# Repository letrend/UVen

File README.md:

# UVen
UV irradiation system for enhanced photo-activation in living cells

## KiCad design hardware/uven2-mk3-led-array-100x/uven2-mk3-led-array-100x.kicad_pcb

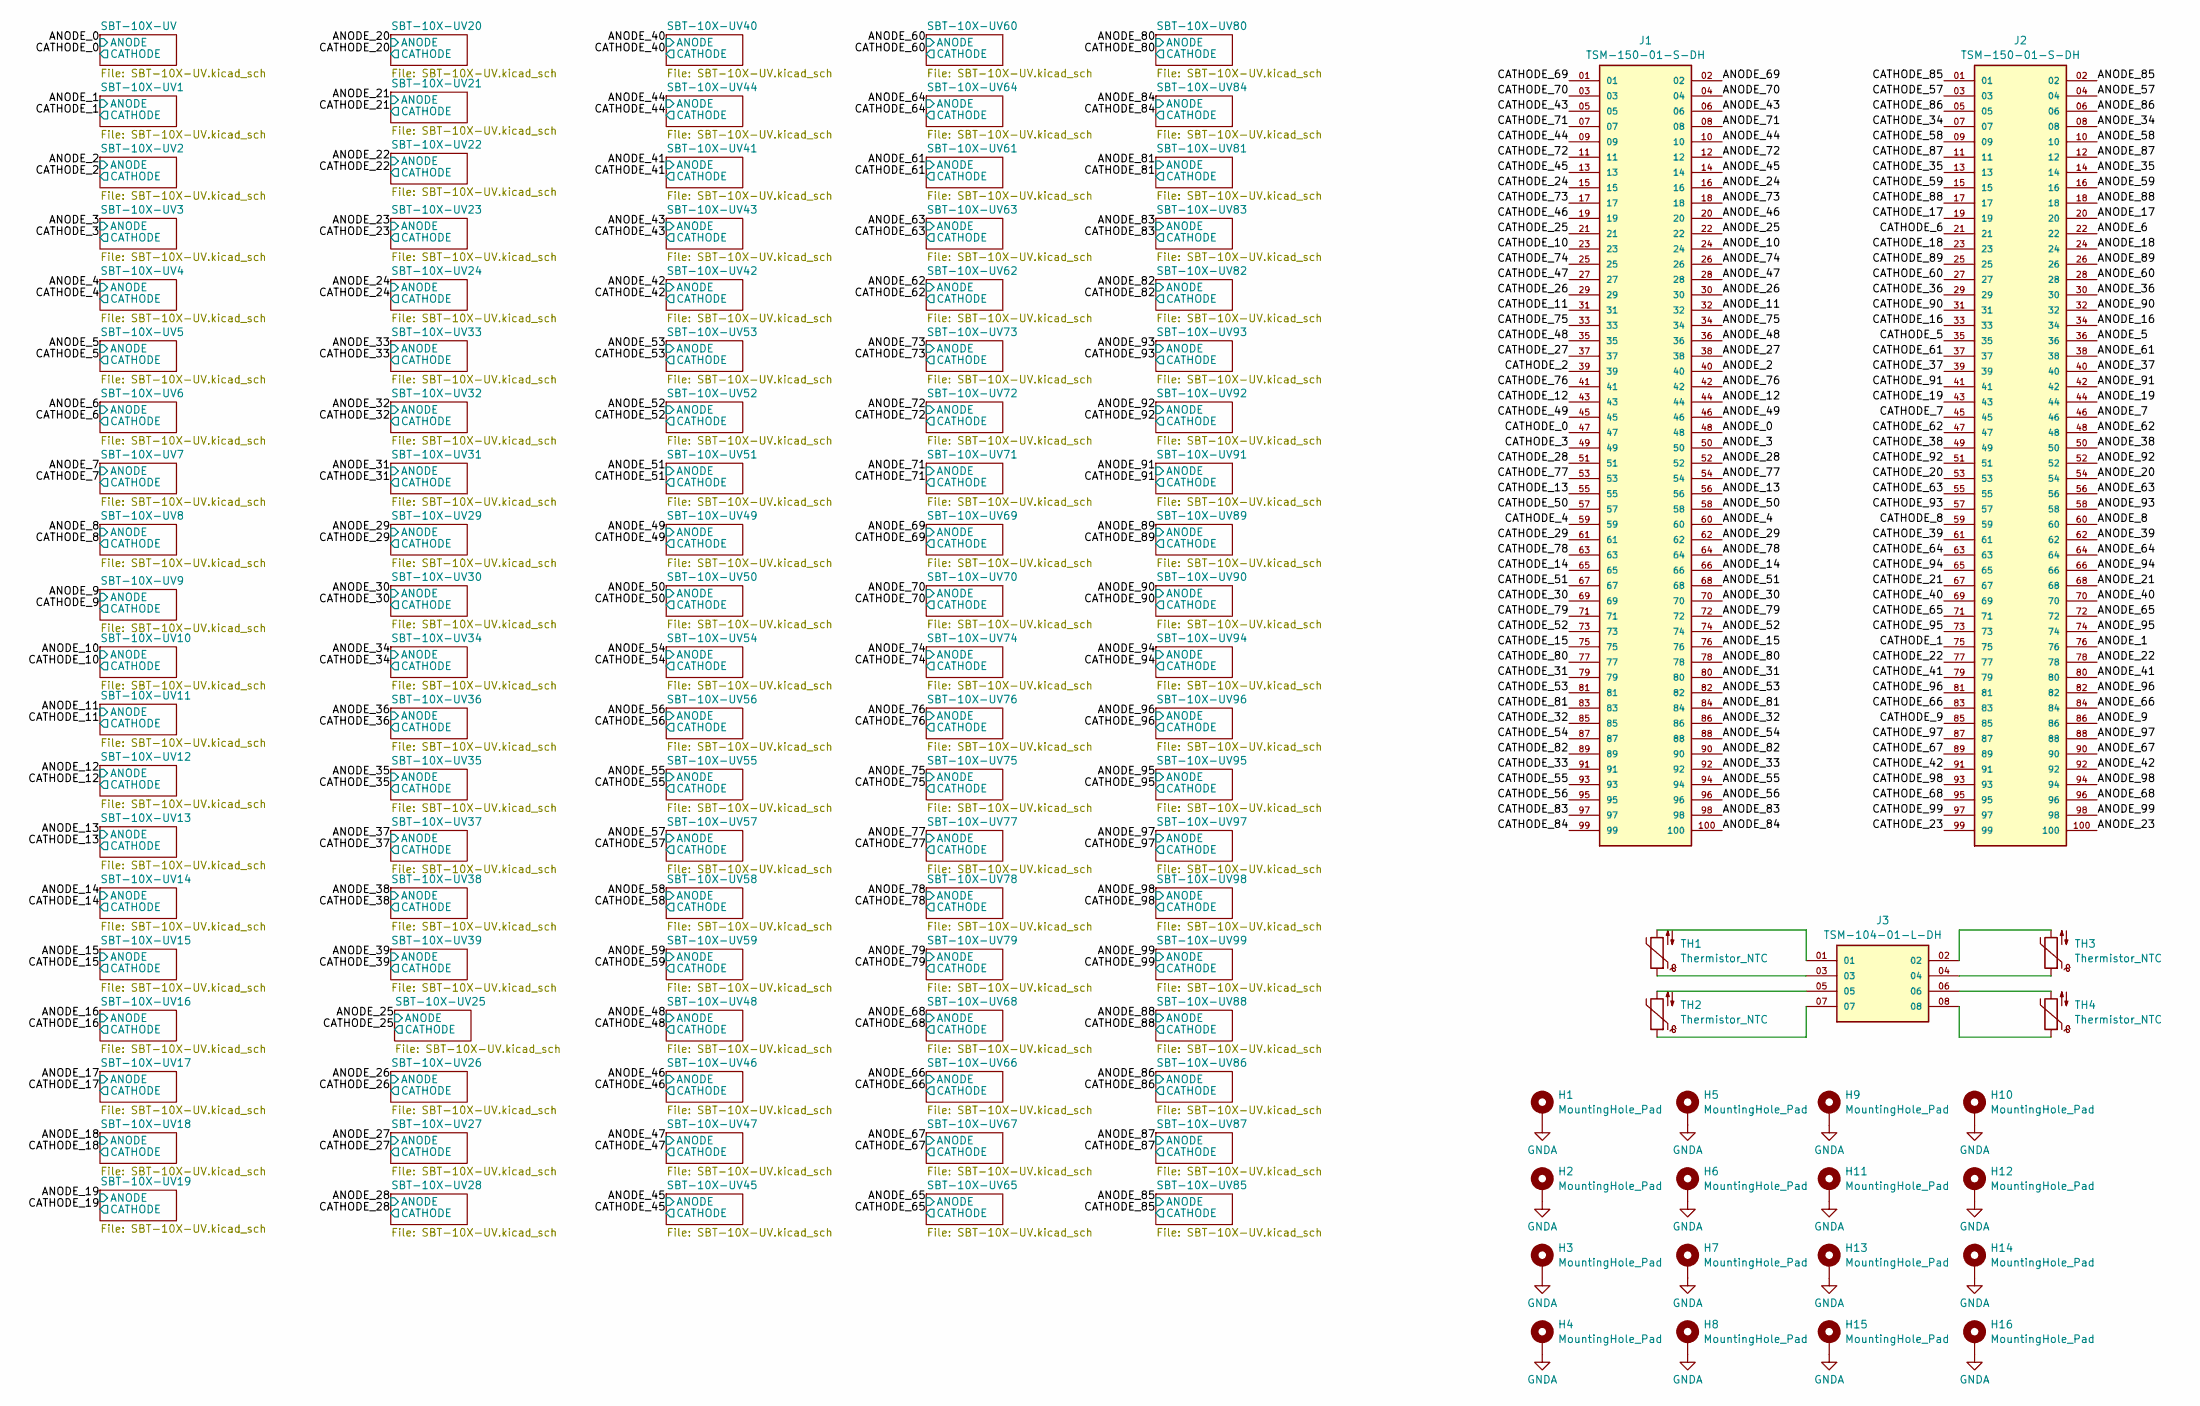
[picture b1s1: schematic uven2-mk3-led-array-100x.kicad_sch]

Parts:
H1, H2, H3, H4, H5, H6, H7, H8, H9, H10, H11, H12, H13, H14, H15, H16: MountingHole_Pad; MountingHole_3.2mm_M3_DIN965_Pad
J1, J2: TSM-150-01-S-DH; SAMTEC_TSM-150-01-S-DH; PARTREV R
J3: TSM-104-01-L-DH; SAMTEC_TSM-104-01-L-DH; PARTREV R
TH1, TH2, TH3, TH4: Thermistor_NTC; R_0805_2012Metric

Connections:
/ANODE_0: J1.48; also elsewhere on the board
/ANODE_1: J2.76; also elsewhere on the board
/ANODE_2: J1.40; also elsewhere on the board
/ANODE_3: J1.50; also elsewhere on the board
/ANODE_4: J1.60; also elsewhere on the board
/ANODE_5: J2.36; also elsewhere on the board
/ANODE_6: J2.22; also elsewhere on the board
/ANODE_7: J2.46; also elsewhere on the board
/ANODE_8: J2.60; also elsewhere on the board
/ANODE_9: J2.86; also elsewhere on the board
/ANODE_10: J1.24; also elsewhere on the board
/ANODE_11: J1.32; also elsewhere on the board
/ANODE_12: J1.44; also elsewhere on the board
/ANODE_13: J1.56; also elsewhere on the board
/ANODE_14: J1.66; also elsewhere on the board
/ANODE_15: J1.76; also elsewhere on the board
/ANODE_16: J2.34; also elsewhere on the board
/ANODE_17: J2.20; also elsewhere on the board
/ANODE_18: J2.24; also elsewhere on the board
/ANODE_19: J2.44; also elsewhere on the board
/ANODE_20: J2.54; also elsewhere on the board
/ANODE_21: J2.68; also elsewhere on the board
/ANODE_22: J2.78; also elsewhere on the board
/ANODE_23: J2.100; also elsewhere on the board
/ANODE_24: J1.16; also elsewhere on the board
/ANODE_25: J1.22; also elsewhere on the board
/ANODE_26: J1.30; also elsewhere on the board
/ANODE_27: J1.38; also elsewhere on the board
/ANODE_28: J1.52; also elsewhere on the board
/ANODE_29: J1.62; also elsewhere on the board
/ANODE_30: J1.70; also elsewhere on the board
/ANODE_31: J1.80; also elsewhere on the board
/ANODE_32: J1.86; also elsewhere on the board
/ANODE_33: J1.92; also elsewhere on the board
/ANODE_34: J2.08; also elsewhere on the board
/ANODE_35: J2.14; also elsewhere on the board
/ANODE_36: J2.30; also elsewhere on the board
/ANODE_37: J2.40; also elsewhere on the board
/ANODE_38: J2.50; also elsewhere on the board
/ANODE_39: J2.62; also elsewhere on the board
/ANODE_40: J2.70; also elsewhere on the board
/ANODE_41: J2.80; also elsewhere on the board
/ANODE_42: J2.92; also elsewhere on the board
/ANODE_43: J1.06; also elsewhere on the board
/ANODE_44: J1.10; also elsewhere on the board
/ANODE_45: J1.14; also elsewhere on the board
/ANODE_46: J1.20; also elsewhere on the board
/ANODE_47: J1.28; also elsewhere on the board
/ANODE_48: J1.36; also elsewhere on the board
/ANODE_49: J1.46; also elsewhere on the board
/ANODE_50: J1.58; also elsewhere on the board
/ANODE_51: J1.68; also elsewhere on the board
/ANODE_52: J1.74; also elsewhere on the board
/ANODE_53: J1.82; also elsewhere on the board
/ANODE_54: J1.88; also elsewhere on the board
/ANODE_55: J1.94; also elsewhere on the board
/ANODE_56: J1.96; also elsewhere on the board
/ANODE_57: J2.04; also elsewhere on the board
/ANODE_58: J2.10; also elsewhere on the board
/ANODE_59: J2.16; also elsewhere on the board
/ANODE_60: J2.28; also elsewhere on the board
/ANODE_61: J2.38; also elsewhere on the board
/ANODE_62: J2.48; also elsewhere on the board
/ANODE_63: J2.56; also elsewhere on the board
/ANODE_64: J2.64; also elsewhere on the board
/ANODE_65: J2.72; also elsewhere on the board
/ANODE_66: J2.84; also elsewhere on the board
/ANODE_67: J2.90; also elsewhere on the board
/ANODE_68: J2.96; also elsewhere on the board
/ANODE_69: J1.02; also elsewhere on the board
/ANODE_70: J1.04; also elsewhere on the board
/ANODE_71: J1.08; also elsewhere on the board
/ANODE_72: J1.12; also elsewhere on the board
/ANODE_73: J1.18; also elsewhere on the board
/ANODE_74: J1.26; also elsewhere on the board
/ANODE_75: J1.34; also elsewhere on the board
/ANODE_76: J1.42; also elsewhere on the board
/ANODE_77: J1.54; also elsewhere on the board
/ANODE_78: J1.64; also elsewhere on the board
/ANODE_79: J1.72; also elsewhere on the board
/ANODE_80: J1.78; also elsewhere on the board
/ANODE_81: J1.84; also elsewhere on the board
/ANODE_82: J1.90; also elsewhere on the board
/ANODE_83: J1.98; also elsewhere on the board
/ANODE_84: J1.100; also elsewhere on the board
/ANODE_85: J2.02; also elsewhere on the board
/ANODE_86: J2.06; also elsewhere on the board
/ANODE_87: J2.12; also elsewhere on the board
/ANODE_88: J2.18; also elsewhere on the board
/ANODE_89: J2.26; also elsewhere on the board
/ANODE_90: J2.32; also elsewhere on the board
/ANODE_91: J2.42; also elsewhere on the board
/ANODE_92: J2.52; also elsewhere on the board
/ANODE_93: J2.58; also elsewhere on the board
/ANODE_94: J2.66; also elsewhere on the board
/ANODE_95: J2.74; also elsewhere on the board
/ANODE_96: J2.82; also elsewhere on the board
/ANODE_97: J2.88; also elsewhere on the board
/ANODE_98: J2.94; also elsewhere on the board
/ANODE_99: J2.98; also elsewhere on the board
/CATHODE_0: J1.47; also elsewhere on the board
/CATHODE_1: J2.75; also elsewhere on the board
/CATHODE_2: J1.39; also elsewhere on the board
/CATHODE_3: J1.49; also elsewhere on the board
/CATHODE_4: J1.59; also elsewhere on the board
/CATHODE_5: J2.35; also elsewhere on the board
/CATHODE_6: J2.21; also elsewhere on the board
/CATHODE_7: J2.45; also elsewhere on the board
/CATHODE_8: J2.59; also elsewhere on the board
/CATHODE_9: J2.85; also elsewhere on the board
/CATHODE_10: J1.23; also elsewhere on the board
/CATHODE_11: J1.31; also elsewhere on the board
/CATHODE_12: J1.43; also elsewhere on the board
/CATHODE_13: J1.55; also elsewhere on the board
/CATHODE_14: J1.65; also elsewhere on the board
/CATHODE_15: J1.75; also elsewhere on the board
/CATHODE_16: J2.33; also elsewhere on the board
/CATHODE_17: J2.19; also elsewhere on the board
/CATHODE_18: J2.23; also elsewhere on the board
/CATHODE_19: J2.43; also elsewhere on the board
/CATHODE_20: J2.53; also elsewhere on the board
/CATHODE_21: J2.67; also elsewhere on the board
/CATHODE_22: J2.77; also elsewhere on the board
/CATHODE_23: J2.99; also elsewhere on the board
/CATHODE_24: J1.15; also elsewhere on the board
/CATHODE_25: J1.21; also elsewhere on the board
/CATHODE_26: J1.29; also elsewhere on the board
/CATHODE_27: J1.37; also elsewhere on the board
/CATHODE_28: J1.51; also elsewhere on the board
/CATHODE_29: J1.61; also elsewhere on the board
/CATHODE_30: J1.69; also elsewhere on the board
/CATHODE_31: J1.79; also elsewhere on the board
/CATHODE_32: J1.85; also elsewhere on the board
/CATHODE_33: J1.91; also elsewhere on the board
/CATHODE_34: J2.07; also elsewhere on the board
/CATHODE_35: J2.13; also elsewhere on the board
/CATHODE_36: J2.29; also elsewhere on the board
/CATHODE_37: J2.39; also elsewhere on the board
/CATHODE_38: J2.49; also elsewhere on the board
/CATHODE_39: J2.61; also elsewhere on the board
/CATHODE_40: J2.69; also elsewhere on the board
/CATHODE_41: J2.79; also elsewhere on the board
/CATHODE_42: J2.91; also elsewhere on the board
/CATHODE_43: J1.05; also elsewhere on the board
/CATHODE_44: J1.09; also elsewhere on the board
/CATHODE_45: J1.13; also elsewhere on the board
/CATHODE_46: J1.19; also elsewhere on the board
/CATHODE_47: J1.27; also elsewhere on the board
/CATHODE_48: J1.35; also elsewhere on the board
/CATHODE_49: J1.45; also elsewhere on the board
/CATHODE_50: J1.57; also elsewhere on the board
/CATHODE_51: J1.67; also elsewhere on the board
/CATHODE_52: J1.73; also elsewhere on the board
/CATHODE_53: J1.81; also elsewhere on the board
/CATHODE_54: J1.87; also elsewhere on the board
/CATHODE_55: J1.93; also elsewhere on the board
/CATHODE_56: J1.95; also elsewhere on the board
/CATHODE_57: J2.03; also elsewhere on the board
/CATHODE_58: J2.09; also elsewhere on the board
/CATHODE_59: J2.15; also elsewhere on the board
/CATHODE_60: J2.27; also elsewhere on the board
/CATHODE_61: J2.37; also elsewhere on the board
/CATHODE_62: J2.47; also elsewhere on the board
/CATHODE_63: J2.55; also elsewhere on the board
/CATHODE_64: J2.63; also elsewhere on the board
/CATHODE_65: J2.71; also elsewhere on the board
/CATHODE_66: J2.83; also elsewhere on the board
/CATHODE_67: J2.89; also elsewhere on the board
/CATHODE_68: J2.95; also elsewhere on the board
/CATHODE_69: J1.01; also elsewhere on the board
/CATHODE_70: J1.03; also elsewhere on the board
/CATHODE_71: J1.07; also elsewhere on the board
/CATHODE_72: J1.11; also elsewhere on the board
/CATHODE_73: J1.17; also elsewhere on the board
/CATHODE_74: J1.25; also elsewhere on the board
/CATHODE_75: J1.33; also elsewhere on the board
/CATHODE_76: J1.41; also elsewhere on the board
/CATHODE_77: J1.53; also elsewhere on the board
/CATHODE_78: J1.63; also elsewhere on the board
/CATHODE_79: J1.71; also elsewhere on the board
/CATHODE_80: J1.77; also elsewhere on the board
/CATHODE_81: J1.83; also elsewhere on the board
/CATHODE_82: J1.89; also elsewhere on the board
/CATHODE_83: J1.97; also elsewhere on the board
/CATHODE_84: J1.99; also elsewhere on the board
/CATHODE_85: J2.01; also elsewhere on the board
/CATHODE_86: J2.05; also elsewhere on the board
/CATHODE_87: J2.11; also elsewhere on the board
/CATHODE_88: J2.17; also elsewhere on the board
/CATHODE_89: J2.25; also elsewhere on the board
/CATHODE_90: J2.31; also elsewhere on the board
/CATHODE_91: J2.41; also elsewhere on the board
/CATHODE_92: J2.51; also elsewhere on the board
/CATHODE_93: J2.57; also elsewhere on the board
/CATHODE_94: J2.65; also elsewhere on the board
/CATHODE_95: J2.73; also elsewhere on the board
/CATHODE_96: J2.81; also elsewhere on the board
/CATHODE_97: J2.87; also elsewhere on the board
/CATHODE_98: J2.93; also elsewhere on the board
/CATHODE_99: J2.97; also elsewhere on the board
GNDA: H1.1, H2.1, H3.1, H4.1, H5.1, H6.1, H7.1, H8.1, H9.1, H10.1, H11.1, H12.1, H13.1, H14.1, H15.1, H16.1
unnamed: J3.01, TH1.2
unnamed: J3.02, TH3.2
unnamed: J3.03, TH1.1
unnamed: J3.04, TH3.1
unnamed: J3.05, TH2.2
unnamed: J3.06, TH4.2
unnamed: J3.07, TH2.1
unnamed: J3.08, TH4.1

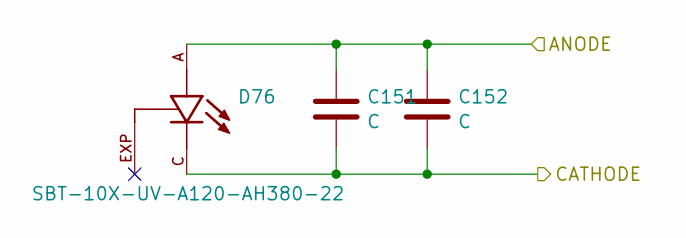
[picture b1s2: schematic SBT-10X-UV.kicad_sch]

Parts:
C151: C; C_0805_2012Metric_Pad1.18x1.45mm_HandSolder
C152: C; C_1206_3216Metric_Pad1.33x1.80mm_HandSolder
D76: SBT-10X-UV-A120-AH380-22; LED_SBT-10X-UV-A120-AH380-22; PARTREV 01

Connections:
/ANODE_75: C151.1, C152.1, D76.A; also elsewhere on the board
/CATHODE_75: C151.2, C152.2, D76.C; also elsewhere on the board

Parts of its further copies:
C1, C3, C5, C7, C9, C11, C13, C15, C17, C19, C21, C23, C25, C27, C29, C31, C33, C35, C37, C39, C41, C43, C45, C47, C49, C51, C53, C55, C57, C59, C61, C63, C65, C67, C69, C71, C73, C75, C77, C79, C81, C83, C85, C87, C89, C91, C93, C95, C97, C99, C101, C103, C105, C107, C109, C111, C113, C115, C117, C119, C121, C123, C125, C127, C129, C131, C133, C135, C137, C139, C141, C143, C145, C147, C149, C153, C155, C157, C159, C161, C163, C165, C167, C169, C171, C173, C175, C177, C179, C181, C183, C185, C187, C189, C191, C193, C195, C197, C199: C; C_0805_2012Metric_Pad1.18x1.45mm_HandSolder
C2, C4, C6, C8, C10, C12, C14, C16, C18, C20, C22, C24, C26, C28, C30, C32, C34, C36, C38, C40, C42, C44, C46, C48, C50, C52, C54, C56, C58, C60, C62, C64, C66, C68, C70, C72, C74, C76, C78, C80, C82, C84, C86, C88, C90, C92, C94, C96, C98, C100, C102, C104, C106, C108, C110, C112, C114, C116, C118, C120, C122, C124, C126, C128, C130, C132, C134, C136, C138, C140, C142, C144, C146, C148, C150, C154, C156, C158, C160, C162, C164, C166, C168, C170, C172, C174, C176, C178, C180, C182, C184, C186, C188, C190, C192, C194, C196, C198, C200: C; C_1206_3216Metric_Pad1.33x1.80mm_HandSolder
D1, D2, D3, D4, D5, D6, D7, D8, D9, D10, D11, D12, D13, D14, D15, D16, D17, D18, D19, D20, D21, D22, D23, D24, D25, D26, D27, D28, D29, D30, D31, D32, D33, D34, D35, D36, D37, D38, D39, D40, D41, D42, D43, D44, D45, D46, D47, D48, D49, D50, D51, D52, D53, D54, D55, D56, D57, D58, D59, D60, D61, D62, D63, D64, D65, D66, D67, D68, D69, D70, D71, D72, D73, D74, D75, D77, D78, D79, D80, D81, D82, D83, D84, D85, D86, D87, D88, D89, D90, D91, D92, D93, D94, D95, D96, D97, D98, D99, D100: SBT-10X-UV-A120-AH380-22; LED_SBT-10X-UV-A120-AH380-22; PARTREV 01

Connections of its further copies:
/ANODE_0: C1.1, C2.1, D1.A; also elsewhere on the board
/ANODE_1: C3.1, C4.1, D2.A; also elsewhere on the board
/ANODE_2: C5.1, C6.1, D3.A; also elsewhere on the board
/ANODE_3: C7.1, C8.1, D4.A; also elsewhere on the board
/ANODE_4: C9.1, C10.1, D5.A; also elsewhere on the board
/ANODE_5: C11.1, C12.1, D6.A; also elsewhere on the board
/ANODE_6: C13.1, C14.1, D7.A; also elsewhere on the board
/ANODE_7: C15.1, C16.1, D8.A; also elsewhere on the board
/ANODE_8: C17.1, C18.1, D9.A; also elsewhere on the board
/ANODE_9: C19.1, C20.1, D10.A; also elsewhere on the board
/ANODE_10: C21.1, C22.1, D11.A; also elsewhere on the board
/ANODE_11: C23.1, C24.1, D12.A; also elsewhere on the board
/ANODE_12: C25.1, C26.1, D13.A; also elsewhere on the board
/ANODE_13: C27.1, C28.1, D14.A; also elsewhere on the board
/ANODE_14: C29.1, C30.1, D15.A; also elsewhere on the board
/ANODE_15: C31.1, C32.1, D16.A; also elsewhere on the board
/ANODE_16: C33.1, C34.1, D17.A; also elsewhere on the board
/ANODE_17: C35.1, C36.1, D18.A; also elsewhere on the board
/ANODE_18: C37.1, C38.1, D19.A; also elsewhere on the board
/ANODE_19: C39.1, C40.1, D20.A; also elsewhere on the board
/ANODE_20: C41.1, C42.1, D21.A; also elsewhere on the board
/ANODE_21: C43.1, C44.1, D22.A; also elsewhere on the board
/ANODE_22: C45.1, C46.1, D23.A; also elsewhere on the board
/ANODE_23: C47.1, C48.1, D24.A; also elsewhere on the board
/ANODE_24: C49.1, C50.1, D25.A; also elsewhere on the board
/ANODE_25: C51.1, C52.1, D26.A; also elsewhere on the board
/ANODE_26: C53.1, C54.1, D27.A; also elsewhere on the board
/ANODE_27: C55.1, C56.1, D28.A; also elsewhere on the board
/ANODE_28: C57.1, C58.1, D29.A; also elsewhere on the board
/ANODE_29: C59.1, C60.1, D30.A; also elsewhere on the board
/ANODE_30: C61.1, C62.1, D31.A; also elsewhere on the board
/ANODE_31: C63.1, C64.1, D32.A; also elsewhere on the board
/ANODE_32: C65.1, C66.1, D33.A; also elsewhere on the board
/ANODE_33: C67.1, C68.1, D34.A; also elsewhere on the board
/ANODE_34: C69.1, C70.1, D35.A; also elsewhere on the board
/ANODE_35: C71.1, C72.1, D36.A; also elsewhere on the board
/ANODE_36: C73.1, C74.1, D37.A; also elsewhere on the board
/ANODE_37: C75.1, C76.1, D38.A; also elsewhere on the board
/ANODE_38: C77.1, C78.1, D39.A; also elsewhere on the board
/ANODE_39: C79.1, C80.1, D40.A; also elsewhere on the board
/ANODE_40: C81.1, C82.1, D41.A; also elsewhere on the board
/ANODE_41: C83.1, C84.1, D42.A; also elsewhere on the board
/ANODE_42: C85.1, C86.1, D43.A; also elsewhere on the board
/ANODE_43: C87.1, C88.1, D44.A; also elsewhere on the board
/ANODE_44: C89.1, C90.1, D45.A; also elsewhere on the board
/ANODE_45: C91.1, C92.1, D46.A; also elsewhere on the board
/ANODE_46: C93.1, C94.1, D47.A; also elsewhere on the board
/ANODE_47: C95.1, C96.1, D48.A; also elsewhere on the board
/ANODE_48: C97.1, C98.1, D49.A; also elsewhere on the board
/ANODE_49: C99.1, C100.1, D50.A; also elsewhere on the board
/ANODE_50: C101.1, C102.1, D51.A; also elsewhere on the board
/ANODE_51: C103.1, C104.1, D52.A; also elsewhere on the board
/ANODE_52: C105.1, C106.1, D53.A; also elsewhere on the board
/ANODE_53: C107.1, C108.1, D54.A; also elsewhere on the board
/ANODE_54: C109.1, C110.1, D55.A; also elsewhere on the board
/ANODE_55: C111.1, C112.1, D56.A; also elsewhere on the board
/ANODE_56: C113.1, C114.1, D57.A; also elsewhere on the board
/ANODE_57: C115.1, C116.1, D58.A; also elsewhere on the board
/ANODE_58: C117.1, C118.1, D59.A; also elsewhere on the board
/ANODE_59: C119.1, C120.1, D60.A; also elsewhere on the board
/ANODE_60: C121.1, C122.1, D61.A; also elsewhere on the board
/ANODE_61: C123.1, C124.1, D62.A; also elsewhere on the board
/ANODE_62: C125.1, C126.1, D63.A; also elsewhere on the board
/ANODE_63: C127.1, C128.1, D64.A; also elsewhere on the board
/ANODE_64: C129.1, C130.1, D65.A; also elsewhere on the board
/ANODE_65: C131.1, C132.1, D66.A; also elsewhere on the board
/ANODE_66: C133.1, C134.1, D67.A; also elsewhere on the board
/ANODE_67: C135.1, C136.1, D68.A; also elsewhere on the board
/ANODE_68: C137.1, C138.1, D69.A; also elsewhere on the board
/ANODE_69: C139.1, C140.1, D70.A; also elsewhere on the board
/ANODE_70: C141.1, C142.1, D71.A; also elsewhere on the board
/ANODE_71: C143.1, C144.1, D72.A; also elsewhere on the board
/ANODE_72: C145.1, C146.1, D73.A; also elsewhere on the board
/ANODE_73: C147.1, C148.1, D74.A; also elsewhere on the board
/ANODE_74: C149.1, C150.1, D75.A; also elsewhere on the board
/ANODE_76: C153.1, C154.1, D77.A; also elsewhere on the board
/ANODE_77: C155.1, C156.1, D78.A; also elsewhere on the board
/ANODE_78: C157.1, C158.1, D79.A; also elsewhere on the board
/ANODE_79: C159.1, C160.1, D80.A; also elsewhere on the board
/ANODE_80: C161.1, C162.1, D81.A; also elsewhere on the board
/ANODE_81: C163.1, C164.1, D82.A; also elsewhere on the board
/ANODE_82: C165.1, C166.1, D83.A; also elsewhere on the board
/ANODE_83: C167.1, C168.1, D84.A; also elsewhere on the board
/ANODE_84: C169.1, C170.1, D85.A; also elsewhere on the board
/ANODE_85: C171.1, C172.1, D86.A; also elsewhere on the board
/ANODE_86: C173.1, C174.1, D87.A; also elsewhere on the board
/ANODE_87: C175.1, C176.1, D88.A; also elsewhere on the board
/ANODE_88: C177.1, C178.1, D89.A; also elsewhere on the board
/ANODE_89: C179.1, C180.1, D90.A; also elsewhere on the board
/ANODE_90: C181.1, C182.1, D91.A; also elsewhere on the board
/ANODE_91: C183.1, C184.1, D92.A; also elsewhere on the board
/ANODE_92: C185.1, C186.1, D93.A; also elsewhere on the board
/ANODE_93: C187.1, C188.1, D94.A; also elsewhere on the board
/ANODE_94: C189.1, C190.1, D95.A; also elsewhere on the board
/ANODE_95: C191.1, C192.1, D96.A; also elsewhere on the board
/ANODE_96: C193.1, C194.1, D97.A; also elsewhere on the board
/ANODE_97: C195.1, C196.1, D98.A; also elsewhere on the board
/ANODE_98: C197.1, C198.1, D99.A; also elsewhere on the board
/ANODE_99: C199.1, C200.1, D100.A; also elsewhere on the board
/CATHODE_0: C1.2, C2.2, D1.C; also elsewhere on the board
/CATHODE_1: C3.2, C4.2, D2.C; also elsewhere on the board
/CATHODE_2: C5.2, C6.2, D3.C; also elsewhere on the board
/CATHODE_3: C7.2, C8.2, D4.C; also elsewhere on the board
/CATHODE_4: C9.2, C10.2, D5.C; also elsewhere on the board
/CATHODE_5: C11.2, C12.2, D6.C; also elsewhere on the board
/CATHODE_6: C13.2, C14.2, D7.C; also elsewhere on the board
/CATHODE_7: C15.2, C16.2, D8.C; also elsewhere on the board
/CATHODE_8: C17.2, C18.2, D9.C; also elsewhere on the board
/CATHODE_9: C19.2, C20.2, D10.C; also elsewhere on the board
/CATHODE_10: C21.2, C22.2, D11.C; also elsewhere on the board
/CATHODE_11: C23.2, C24.2, D12.C; also elsewhere on the board
/CATHODE_12: C25.2, C26.2, D13.C; also elsewhere on the board
/CATHODE_13: C27.2, C28.2, D14.C; also elsewhere on the board
/CATHODE_14: C29.2, C30.2, D15.C; also elsewhere on the board
/CATHODE_15: C31.2, C32.2, D16.C; also elsewhere on the board
/CATHODE_16: C33.2, C34.2, D17.C; also elsewhere on the board
/CATHODE_17: C35.2, C36.2, D18.C; also elsewhere on the board
/CATHODE_18: C37.2, C38.2, D19.C; also elsewhere on the board
/CATHODE_19: C39.2, C40.2, D20.C; also elsewhere on the board
/CATHODE_20: C41.2, C42.2, D21.C; also elsewhere on the board
/CATHODE_21: C43.2, C44.2, D22.C; also elsewhere on the board
/CATHODE_22: C45.2, C46.2, D23.C; also elsewhere on the board
/CATHODE_23: C47.2, C48.2, D24.C; also elsewhere on the board
/CATHODE_24: C49.2, C50.2, D25.C; also elsewhere on the board
/CATHODE_25: C51.2, C52.2, D26.C; also elsewhere on the board
/CATHODE_26: C53.2, C54.2, D27.C; also elsewhere on the board
/CATHODE_27: C55.2, C56.2, D28.C; also elsewhere on the board
/CATHODE_28: C57.2, C58.2, D29.C; also elsewhere on the board
/CATHODE_29: C59.2, C60.2, D30.C; also elsewhere on the board
/CATHODE_30: C61.2, C62.2, D31.C; also elsewhere on the board
/CATHODE_31: C63.2, C64.2, D32.C; also elsewhere on the board
/CATHODE_32: C65.2, C66.2, D33.C; also elsewhere on the board
/CATHODE_33: C67.2, C68.2, D34.C; also elsewhere on the board
/CATHODE_34: C69.2, C70.2, D35.C; also elsewhere on the board
/CATHODE_35: C71.2, C72.2, D36.C; also elsewhere on the board
/CATHODE_36: C73.2, C74.2, D37.C; also elsewhere on the board
/CATHODE_37: C75.2, C76.2, D38.C; also elsewhere on the board
/CATHODE_38: C77.2, C78.2, D39.C; also elsewhere on the board
/CATHODE_39: C79.2, C80.2, D40.C; also elsewhere on the board
/CATHODE_40: C81.2, C82.2, D41.C; also elsewhere on the board
/CATHODE_41: C83.2, C84.2, D42.C; also elsewhere on the board
/CATHODE_42: C85.2, C86.2, D43.C; also elsewhere on the board
/CATHODE_43: C87.2, C88.2, D44.C; also elsewhere on the board
/CATHODE_44: C89.2, C90.2, D45.C; also elsewhere on the board
/CATHODE_45: C91.2, C92.2, D46.C; also elsewhere on the board
/CATHODE_46: C93.2, C94.2, D47.C; also elsewhere on the board
/CATHODE_47: C95.2, C96.2, D48.C; also elsewhere on the board
/CATHODE_48: C97.2, C98.2, D49.C; also elsewhere on the board
/CATHODE_49: C99.2, C100.2, D50.C; also elsewhere on the board
/CATHODE_50: C101.2, C102.2, D51.C; also elsewhere on the board
/CATHODE_51: C103.2, C104.2, D52.C; also elsewhere on the board
/CATHODE_52: C105.2, C106.2, D53.C; also elsewhere on the board
/CATHODE_53: C107.2, C108.2, D54.C; also elsewhere on the board
/CATHODE_54: C109.2, C110.2, D55.C; also elsewhere on the board
/CATHODE_55: C111.2, C112.2, D56.C; also elsewhere on the board
/CATHODE_56: C113.2, C114.2, D57.C; also elsewhere on the board
/CATHODE_57: C115.2, C116.2, D58.C; also elsewhere on the board
/CATHODE_58: C117.2, C118.2, D59.C; also elsewhere on the board
/CATHODE_59: C119.2, C120.2, D60.C; also elsewhere on the board
/CATHODE_60: C121.2, C122.2, D61.C; also elsewhere on the board
/CATHODE_61: C123.2, C124.2, D62.C; also elsewhere on the board
/CATHODE_62: C125.2, C126.2, D63.C; also elsewhere on the board
/CATHODE_63: C127.2, C128.2, D64.C; also elsewhere on the board
/CATHODE_64: C129.2, C130.2, D65.C; also elsewhere on the board
/CATHODE_65: C131.2, C132.2, D66.C; also elsewhere on the board
/CATHODE_66: C133.2, C134.2, D67.C; also elsewhere on the board
/CATHODE_67: C135.2, C136.2, D68.C; also elsewhere on the board
/CATHODE_68: C137.2, C138.2, D69.C; also elsewhere on the board
/CATHODE_69: C139.2, C140.2, D70.C; also elsewhere on the board
/CATHODE_70: C141.2, C142.2, D71.C; also elsewhere on the board
/CATHODE_71: C143.2, C144.2, D72.C; also elsewhere on the board
/CATHODE_72: C145.2, C146.2, D73.C; also elsewhere on the board
/CATHODE_73: C147.2, C148.2, D74.C; also elsewhere on the board
/CATHODE_74: C149.2, C150.2, D75.C; also elsewhere on the board
/CATHODE_76: C153.2, C154.2, D77.C; also elsewhere on the board
/CATHODE_77: C155.2, C156.2, D78.C; also elsewhere on the board
/CATHODE_78: C157.2, C158.2, D79.C; also elsewhere on the board
/CATHODE_79: C159.2, C160.2, D80.C; also elsewhere on the board
/CATHODE_80: C161.2, C162.2, D81.C; also elsewhere on the board
/CATHODE_81: C163.2, C164.2, D82.C; also elsewhere on the board
/CATHODE_82: C165.2, C166.2, D83.C; also elsewhere on the board
/CATHODE_83: C167.2, C168.2, D84.C; also elsewhere on the board
/CATHODE_84: C169.2, C170.2, D85.C; also elsewhere on the board
/CATHODE_85: C171.2, C172.2, D86.C; also elsewhere on the board
/CATHODE_86: C173.2, C174.2, D87.C; also elsewhere on the board
/CATHODE_87: C175.2, C176.2, D88.C; also elsewhere on the board
/CATHODE_88: C177.2, C178.2, D89.C; also elsewhere on the board
/CATHODE_89: C179.2, C180.2, D90.C; also elsewhere on the board
/CATHODE_90: C181.2, C182.2, D91.C; also elsewhere on the board
/CATHODE_91: C183.2, C184.2, D92.C; also elsewhere on the board
/CATHODE_92: C185.2, C186.2, D93.C; also elsewhere on the board
/CATHODE_93: C187.2, C188.2, D94.C; also elsewhere on the board
/CATHODE_94: C189.2, C190.2, D95.C; also elsewhere on the board
/CATHODE_95: C191.2, C192.2, D96.C; also elsewhere on the board
/CATHODE_96: C193.2, C194.2, D97.C; also elsewhere on the board
/CATHODE_97: C195.2, C196.2, D98.C; also elsewhere on the board
/CATHODE_98: C197.2, C198.2, D99.C; also elsewhere on the board
/CATHODE_99: C199.2, C200.2, D100.C; also elsewhere on the board

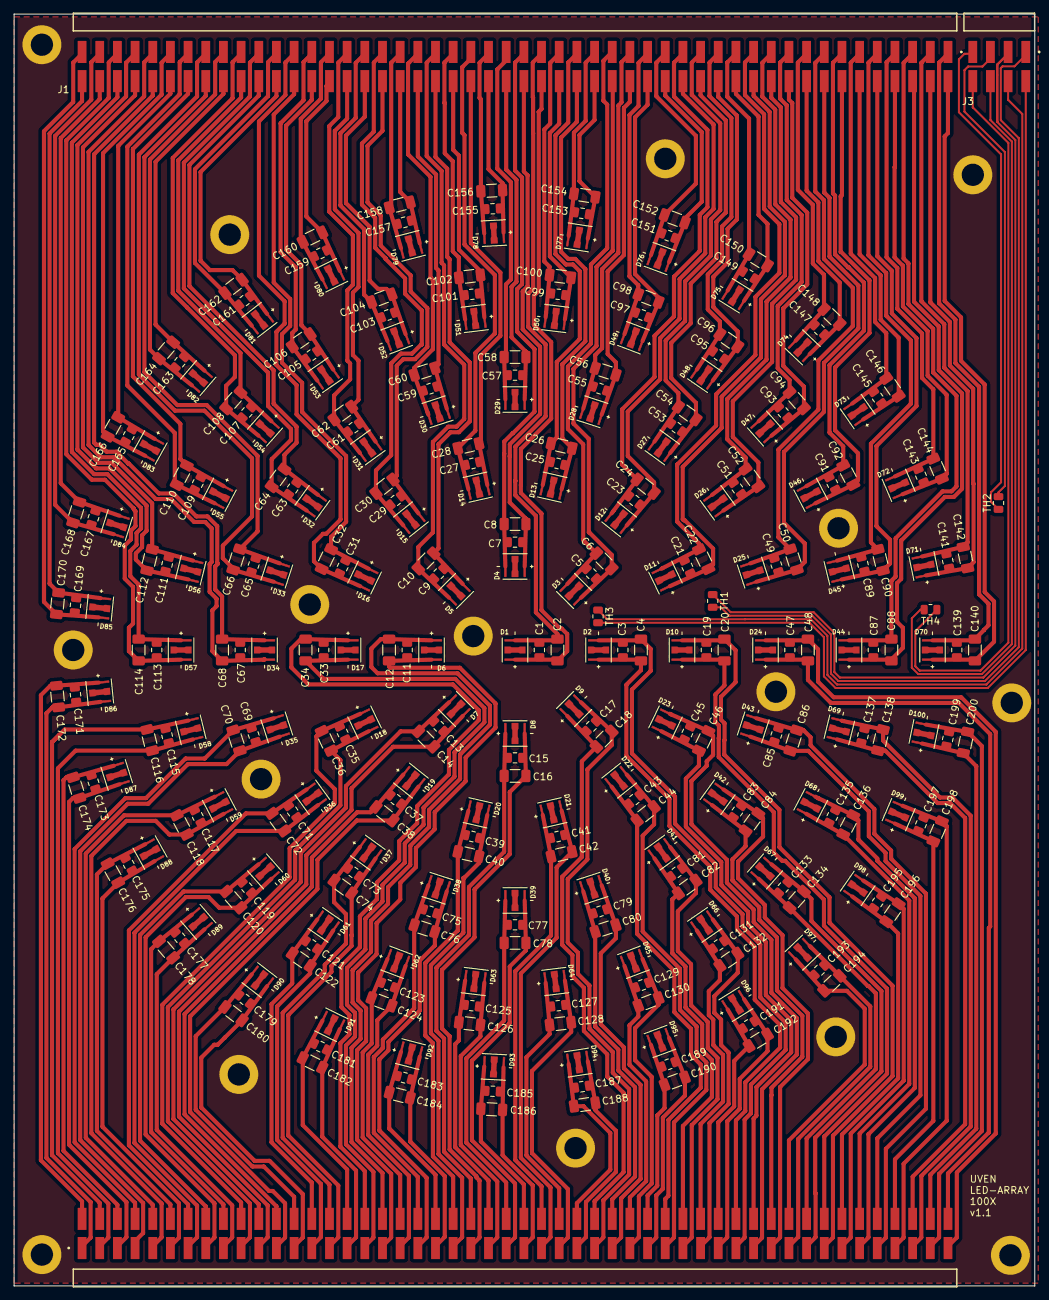
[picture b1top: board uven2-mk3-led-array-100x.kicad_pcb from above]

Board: 2 copper layers, 146.7 x 182.8 mm, 323 parts (0 on the bottom side), 209 nets.

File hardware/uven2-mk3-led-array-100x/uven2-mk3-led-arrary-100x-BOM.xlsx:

Comment | Designator | Footprint | JLCPCB Part #（optional）
1uF | C96,C138,C86,C120,C168,C54,C142,C26,C170,C200,C28,C110,C72,C100,C172,C140,C30,C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 | C_1206_3216Metric_Pad1.33x1.80mm_HandSolder | C1848
100nF | C105,C131,C67,C143,C87,C73,C19,C15,C141,C13,C79,C185,C189,C21,C85,C77,C3,C165,C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 | C_0805_2012Metric_Pad1.18x1.45mm_HandSolder | C1711
SBT-10X-UV-A120-AH365-22 | D21,D29,D41,D22,D14,D32,D51,D26,D68,D12,D76,D72,D98,D58,D36,D64,D31,D16,D4,D96,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 | LED_SBT-10X-UV-A120-AH365-22 | C41711937
Thermistor_NTC | TH1,TH4,TH3,TH2 | R_0805_2012Metric | C17376775
TSM-104-01-L-DH | J3 | SAMTEC_TSM-104-01-L-DH | C6886679
TSM-150-01-S-DH | J2,J1 | SAMTEC_TSM-150-01-S-DH | C7365464

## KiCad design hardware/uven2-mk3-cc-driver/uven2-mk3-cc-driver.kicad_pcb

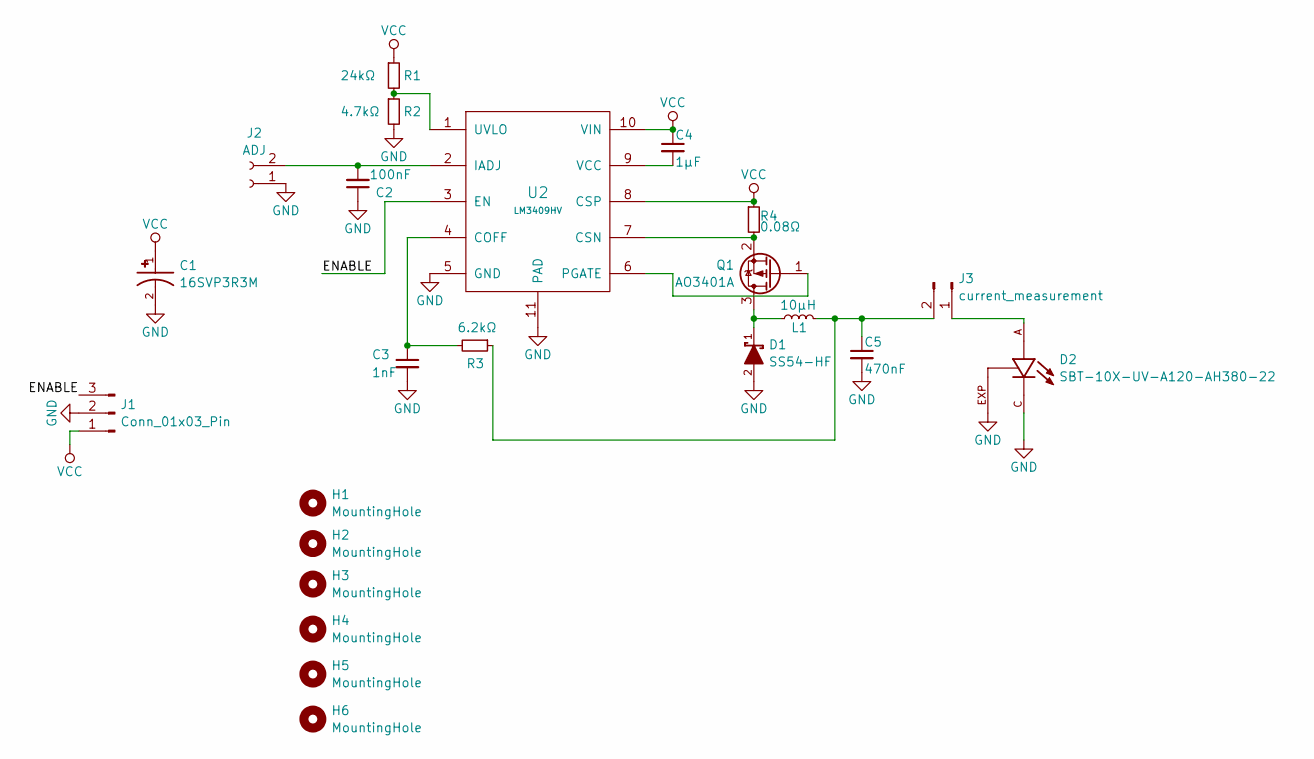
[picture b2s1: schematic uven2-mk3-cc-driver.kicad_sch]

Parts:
C1: 16SVP3R3M; CAP_16SVP3R3M; PARTREV 01-Nov-15
C2: 100nF; C_0603_1608Metric_Pad1.08x0.95mm_HandSolder
C3: 1nF; C_0603_1608Metric_Pad1.08x0.95mm_HandSolder
C4: 1µF; C_0603_1608Metric_Pad1.08x0.95mm_HandSolder
C5: 470nF; C_1812_4532Metric_Pad1.57x3.40mm_HandSolder
D1: SS54-HF; DIOM5025X220N; MOUSER_PART_NUMBER 750-SS54-HF
D2: SBT-10X-UV-A120-AH380-22; LED_SBT-10X-UV-A120-AH380-22; PARTREV 01
H1, H2, H3, H4, H5, H6: MountingHole; MountingHole_2.2mm_M2
J1: Conn_01x03_Pin; PinSocket_1x03_P2.54mm_Vertical
J2: ADJ; PinSocket_1x02_P2.54mm_Vertical
J3: current_measurement; PinHeader_1x02_P2.54mm_Vertical
L1: 10µH; HPC-8040NV-100M
Q1: AO3401A; SOT-23
R1: 24kΩ; R_0603_1608Metric_Pad0.98x0.95mm_HandSolder
R2: 4.7kΩ; R_0603_1608Metric_Pad0.98x0.95mm_HandSolder
R3: 6.2kΩ; R_0603_1608Metric_Pad0.98x0.95mm_HandSolder
R4: 0.08Ω; R_2512_6332Metric_Pad1.40x3.35mm_HandSolder
U2: LM3409HV; IC_XTR111AIDGQR

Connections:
/ENABLE: J1.3, U2.3 (EN)
GND: C1.2, C2.1, C3.2, C5.2, D1.2, D2.C, D2.EXP, J1.2, J2.1, R2.2, U2.5 (GND), U2.11 (PAD)
unnamed: C2.2, J2.2, U2.2 (IADJ)
unnamed: D2.A, J3.1
unnamed: C5.1, J3.2, L1.2, R3.1
unnamed: D1.1, L1.1, Q1.3 (D)
unnamed: Q1.1 (G), U2.6 (PGATE)
unnamed: Q1.2 (S), R4.2, U2.7 (CSN)
unnamed: C3.1, R3.2, U2.4 (COFF)
unnamed: R1.2, R2.1, U2.1 (UVLO)
unnamed: C4.2, U2.9 (VCC)
VCC: C1.1, C4.1, J1.1, R1.1, R4.1, U2.8 (CSP), U2.10 (VIN)

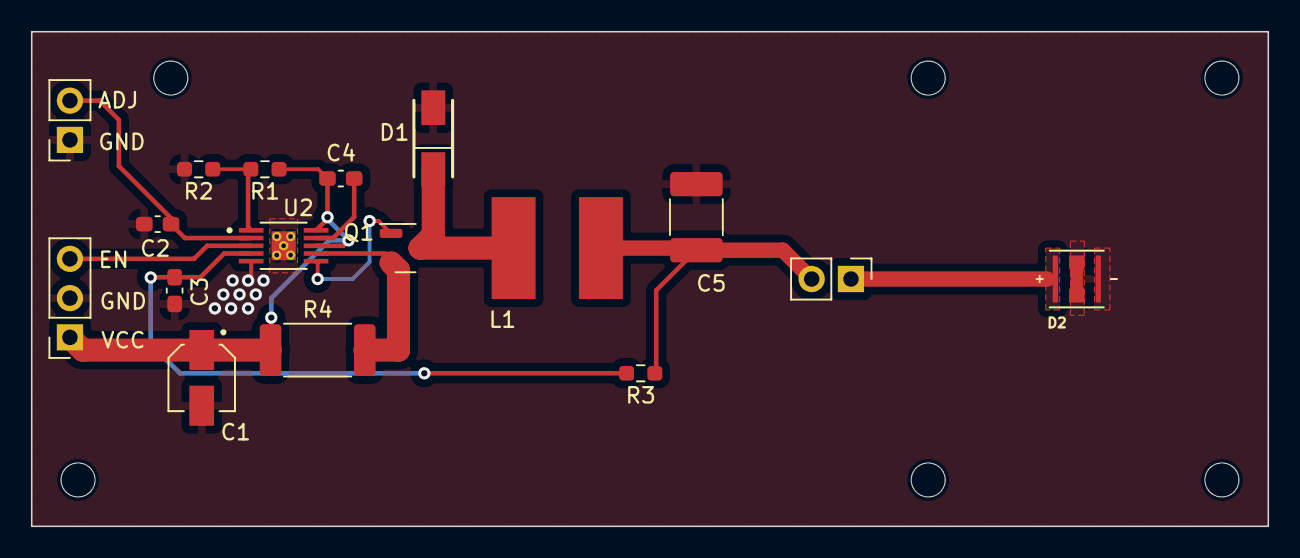
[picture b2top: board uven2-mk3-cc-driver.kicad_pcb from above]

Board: 2 copper layers, 80.0 x 32.0 mm, 23 parts (0 on the bottom side), 12 nets.
